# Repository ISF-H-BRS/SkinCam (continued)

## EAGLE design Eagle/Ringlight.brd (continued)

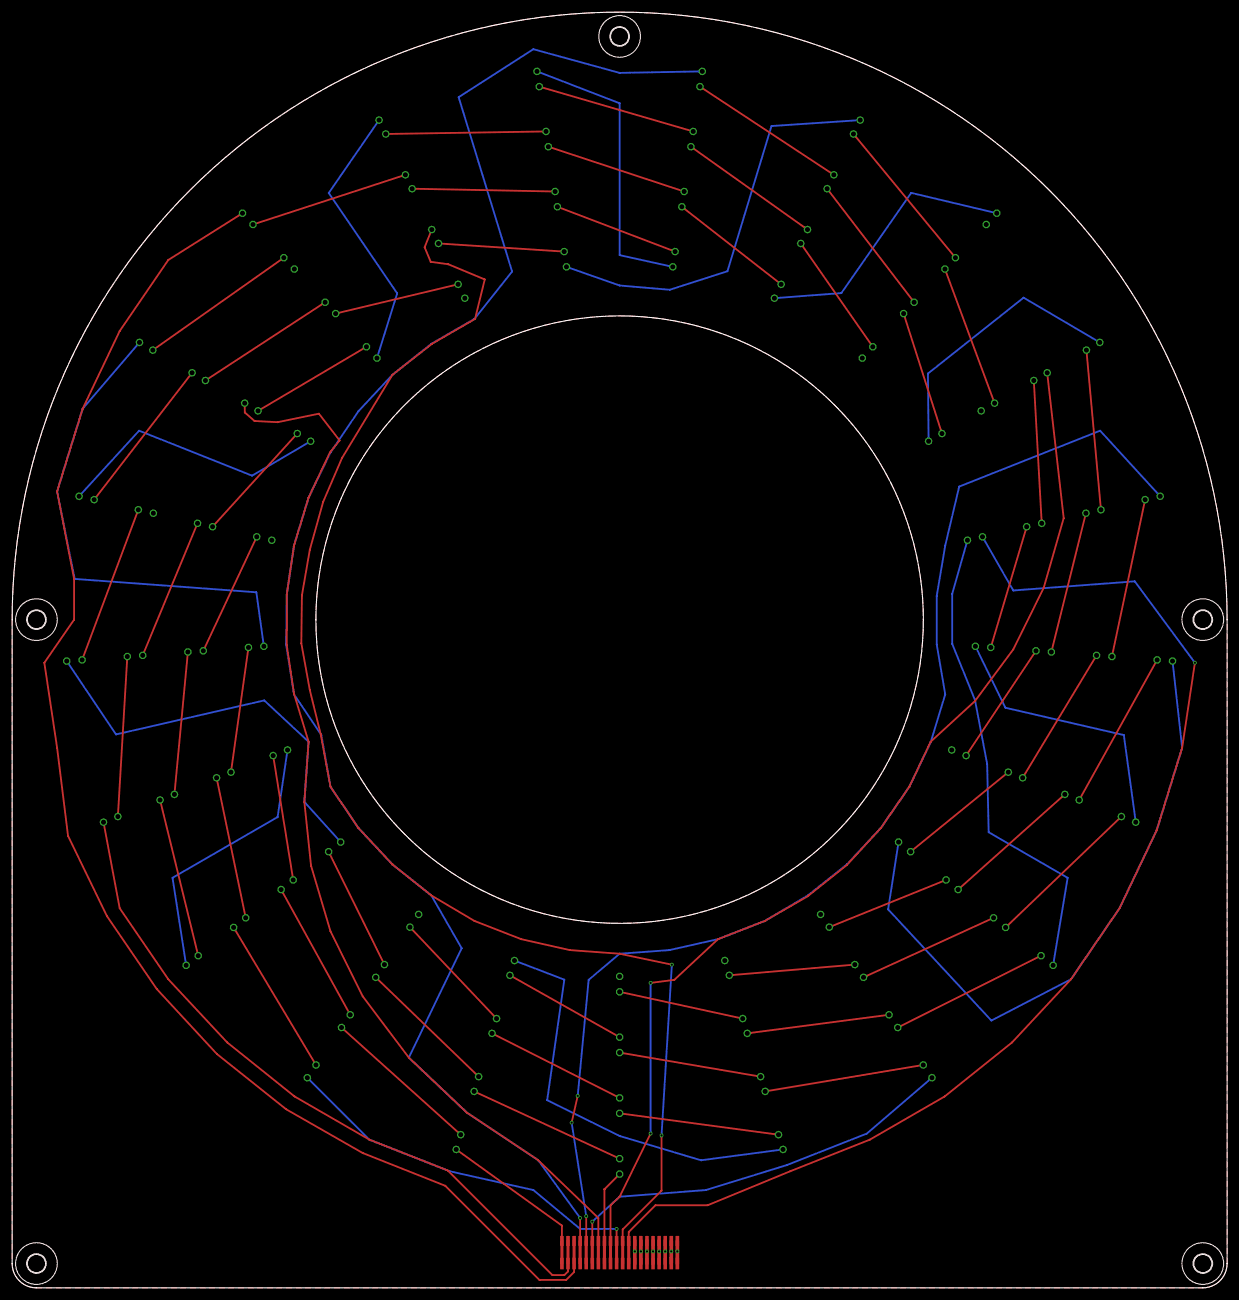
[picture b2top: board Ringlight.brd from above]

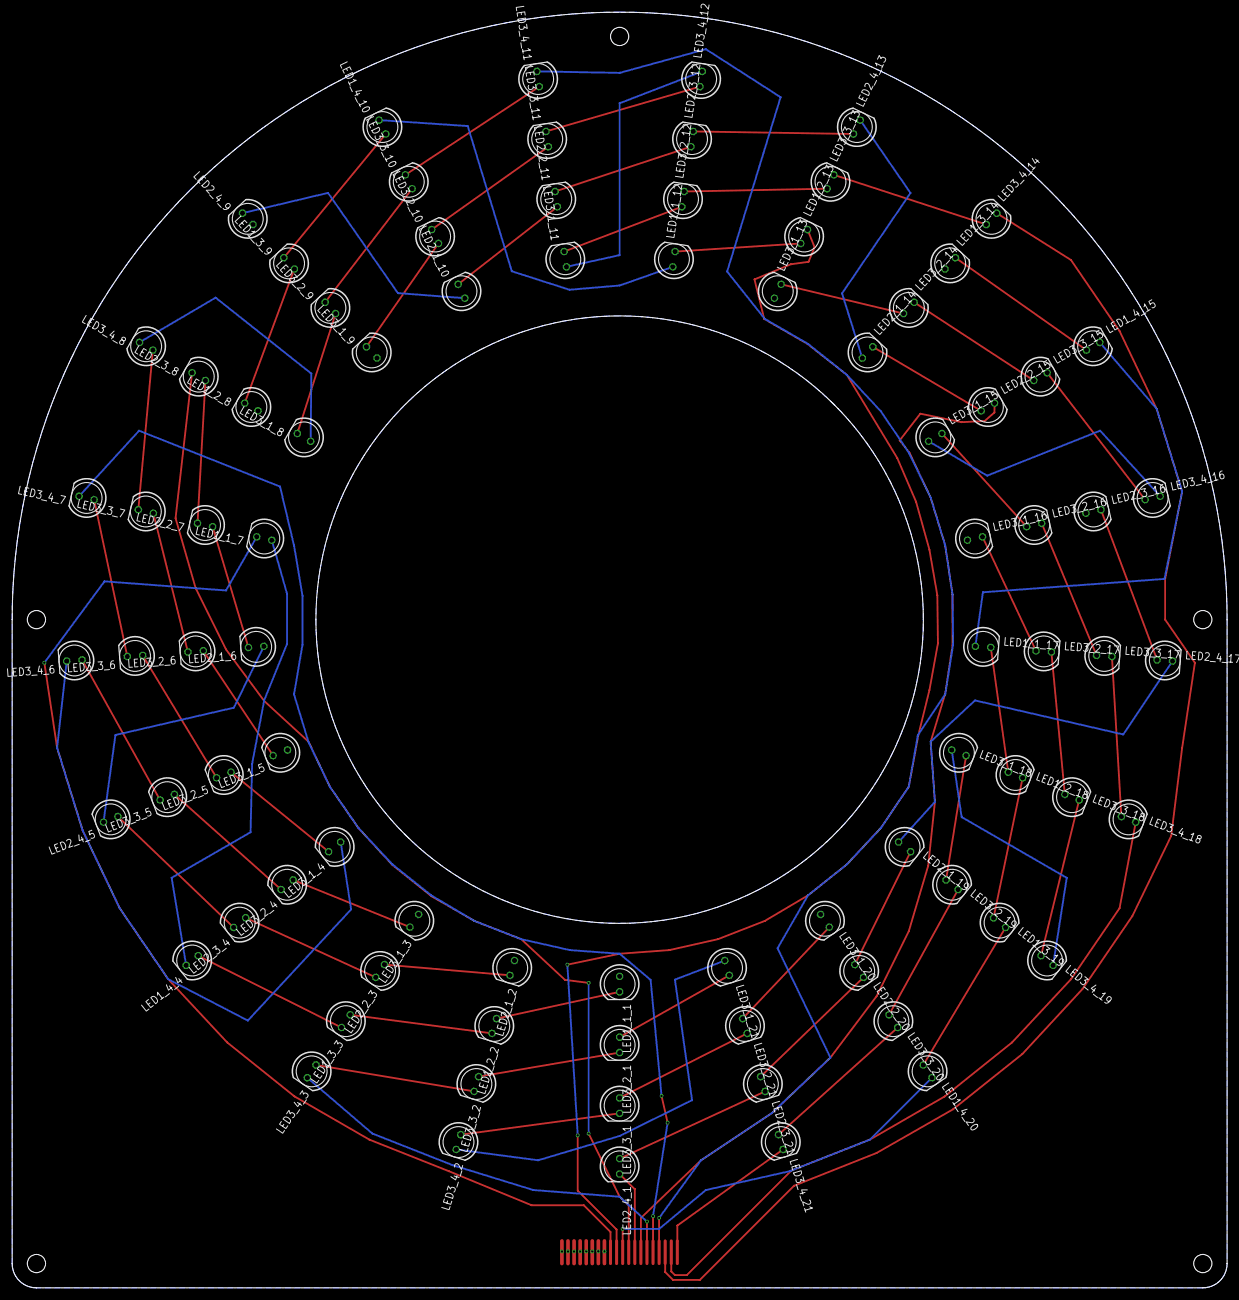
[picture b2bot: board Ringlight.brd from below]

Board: 2 copper layers, 200.0 x 210.0 mm, 90 parts (84 on the bottom side), 85 nets.

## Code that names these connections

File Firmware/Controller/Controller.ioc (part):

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Mcu.Name=STM32L412KBTx
Mcu.Package=LQFP32
Mcu.UserName=STM32L412KBTx
PA0-CK_IN.GPIOParameters=GPIO_PuPd,GPIO_Label
PA0-CK_IN.GPIO_Label=DIM1
PA0-CK_IN.GPIO_PuPd=GPIO_PULLDOWN
PA0-CK_IN.Signal=S_TIM2_CH1
PA1.GPIOParameters=GPIO_PuPd,GPIO_Label
PA1.GPIO_Label=DIM2
PA1.GPIO_PuPd=GPIO_PULLDOWN
PA1.Signal=S_TIM2_CH2
PA11.Mode=Device
PA11.Signal=USB_DM
PA12.Mode=Device
PA12.Signal=USB_DP
PA13\ (JTMS/SWDIO).Mode=Serial_Wire
PA13\ (JTMS/SWDIO).Signal=SYS_JTMS-SWDIO
PA14\ (JTCK/SWCLK).Mode=Serial_Wire
PA14\ (JTCK/SWCLK).Signal=SYS_JTCK-SWCLK
PA15\ (JTDI).GPIOParameters=GPIO_Label
PA15\ (JTDI).GPIO_Label=DEBUG_PIN
PA15\ (JTDI).Signal=GPIO_Output
PA2.GPIOParameters=GPIO_PuPd,GPIO_Label
PA2.GPIO_Label=DIM3
PA2.GPIO_PuPd=GPIO_PULLDOWN
PA2.Signal=S_TIM2_CH3
PA3.GPIOParameters=GPIO_PuPd,GPIO_Label
PA3.GPIO_Label=DIM4
PA3.GPIO_PuPd=GPIO_PULLDOWN
PA3.Signal=S_TIM2_CH4
PA6.GPIOParameters=GPIO_Label
PA6.GPIO_Label=TRIGGER_TTL
PA6.Signal=GPIO_Output
PA7.GPIOParameters=GPIO_Label
PA7.GPIO_Label=TRIGGER_ISO
PA7.Signal=GPIO_Output
PB0.GPIOParameters=GPIO_Label
PB0.GPIO_Label=FEEDBACK_TTL
PB0.Signal=GPIO_Input
PB1.GPIOParameters=GPIO_Label
PB1.GPIO_Label=FEEDBACK_ISO
PB1.Signal=GPIO_Input
PB4\ (NJTRST).GPIOParameters=PinState,GPIO_Label,GPIO_ModeDefaultOutputPP
PB4\ (NJTRST).GPIO_Label=STATUS_GOOD
PB4\ (NJTRST).GPIO_ModeDefaultOutputPP=GPIO_MODE_OUTPUT_OD
PB4\ (NJTRST).PinState=GPIO_PIN_SET
PB4\ (NJTRST).Signal=GPIO_Output
PB5.GPIOParameters=PinState,GPIO_Label,GPIO_ModeDefaultOutputPP
PB5.GPIO_Label=STATUS_BAD
PB5.GPIO_ModeDefaultOutputPP=GPIO_MODE_OUTPUT_OD
PB5.PinState=GPIO_PIN_SET
PB5.Signal=GPIO_Output
PB6.GPIOParameters=GPIO_Label,GPIO_Pu
PB6.GPIO_Label=SCL
PB6.GPIO_Pu=GPIO_NOPULL
PB6.Mode=I2C
PB6.Signal=I2C1_SCL
PB7.GPIOParameters=GPIO_Label,GPIO_Pu
PB7.GPIO_Label=SDA
PB7.GPIO_Pu=GPIO_NOPULL
PB7.Mode=I2C
PB7.Signal=I2C1_SDA
PC14-OSC32_IN\ (PC14).GPIOParameters=GPIO_Label
PC14-OSC32_IN\ (PC14).GPIO_Label=LED_ENABLE
PC14-OSC32_IN\ (PC14).Signal=GPIO_Output
RCC.HSE_VALUE=8000000
RCC.SYSCLKFreq_VALUE=80000000
RCC.SYSCLKSource=RCC_SYSCLKSOURCE_PLLCLK
board=custom

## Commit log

2024-07-22 First public release.
2024-08-11 Update to version 5.1.
    The software can now be built without the Vimba SDK.
